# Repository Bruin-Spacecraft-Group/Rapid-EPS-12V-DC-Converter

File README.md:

# Rapid-EPS-12V-DC-Converter
PCB, operational instructions, other random stuff for use on 12V line for Rapid.

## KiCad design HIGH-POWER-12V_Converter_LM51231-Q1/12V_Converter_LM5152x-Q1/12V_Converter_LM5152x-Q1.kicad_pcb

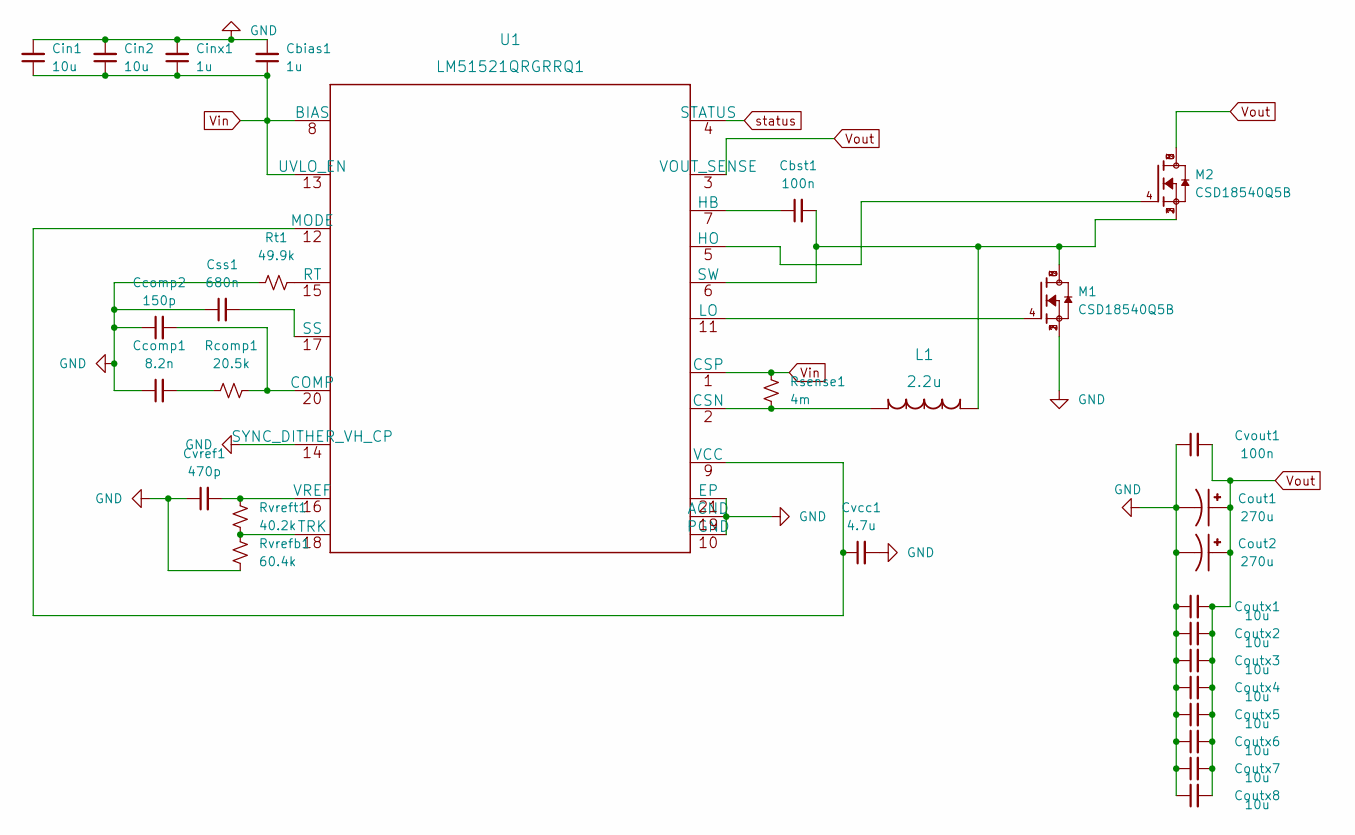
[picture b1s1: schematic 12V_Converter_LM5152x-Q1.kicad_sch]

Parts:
Cbias1: 1u; C_0603_1608Metric; LCSC C92759
Cbst1: 100n; C_0603_1608Metric; LCSC C92759
Ccomp1: 8.2n; C_0805_2012Metric
Ccomp2: 150p; C_0805_2012Metric; LCSC C107111
Cin1, Cin2: 10u; C_1206_3216Metric; LCSC C77093
Cinx1: 1u; C_0603_1608Metric; LCSC C2172920
Cout1, Cout2: 270u; CAP_EEHZS1H271UP
Coutx1, Coutx2, Coutx3, Coutx4, Coutx5, Coutx6, Coutx7, Coutx8: 10u; C_1206_3216Metric; LCSC C77093
Css1: 680n; C_0603_1608Metric
Cvcc1: 4.7u; C_0603_1608Metric
Cvout1: 100n; C_0603_1608Metric; LCSC C2842861
Cvref1: 470p; C_0603_1608Metric; LCSC C85979
L1: 2.2u; IHLP6767GZER2R2M51
M1, M2: CSD18540Q5B; TRANS_CSD18540Q5B; PARTREV B
Rcomp1: 20.5k; R_0603_1608Metric; LCSC C273789
Rsense1: 4m; R_2512_6332Metric
Rt1: 49.9k; R_0603_1608Metric; LCSC C844171
Rvrefb1: 60.4k; R_0603_1608Metric; LCSC C165742
Rvreft1: 40.2k; R_0603_1608Metric; LCSC C844784
U1: LM51521QRGRRQ1

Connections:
GND: Cbias1.2, Ccomp1.1, Ccomp2.1, Cin1.2, Cin2.2, Cinx1.2, Cout1.2, Cout2.2, Coutx1.1, Coutx2.1, Coutx3.1, Coutx4.1, Coutx5.1, Coutx6.1, Coutx7.1, Coutx8.1, Css1.1, Cvcc1.2, Cvout1.1, Cvref1.1, M1.1, M1.2, M1.3, Rt1.1, Rvrefb1.2, U1.10 (PGND), U1.14 (SYNC_DITHER_VH_CP), U1.19 (AGND), U1.21 (EP)
unnamed: Cbst1.1, U1.7 (HB)
unnamed: Cbst1.2, L1.1, M1.5, M1.6, M1.7, M1.8, M2.1, M2.2, M2.3, U1.6 (SW)
unnamed: Ccomp1.2, Rcomp1.1
unnamed: Ccomp2.2, Rcomp1.2, U1.20 (COMP)
unnamed: Css1.2, U1.17 (SS)
unnamed: Cvcc1.1, U1.9 (VCC), U1.12 (MODE)
unnamed: Cvref1.2, Rvreft1.1, U1.16 (VREF)
unnamed: L1.2, Rsense1.2, U1.2 (CSN)
unnamed: M2.4, U1.5 (HO)
unnamed: Rt1.2, U1.15 (RT)
unnamed: Rvrefb1.1, Rvreft1.2, U1.18 (TRK)
unnamed: M1.4, U1.11 (LO)
Vin: Cbias1.1, Cin1.1, Cin2.1, Cinx1.1, Rsense1.1, U1.1 (CSP), U1.8 (BIAS), U1.13 (UVLO_EN)
Vout: Cout1.1, Cout2.1, Coutx1.2, Coutx2.2, Coutx3.2, Coutx4.2, Coutx5.2, Coutx6.2, Coutx7.2, Coutx8.2, Cvout1.2, M2.5, M2.6, M2.7, M2.8, U1.3 (VOUT_SENSE)
status: U1.4 (STATUS); also elsewhere on the board

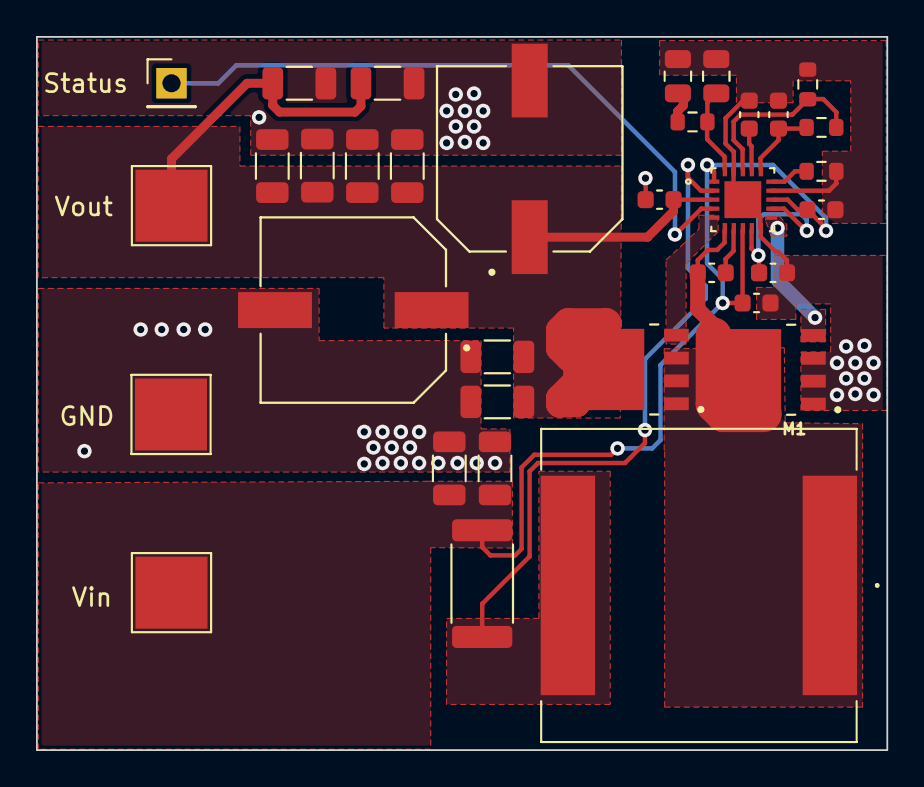
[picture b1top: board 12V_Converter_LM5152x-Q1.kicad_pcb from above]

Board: 2 copper layers, 47.2 x 39.6 mm, 31 parts (0 on the bottom side), 16 nets.

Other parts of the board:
Status: PinHeader_1x01_P2.54mm_Vertical

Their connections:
status: Status.1; also elsewhere on the board

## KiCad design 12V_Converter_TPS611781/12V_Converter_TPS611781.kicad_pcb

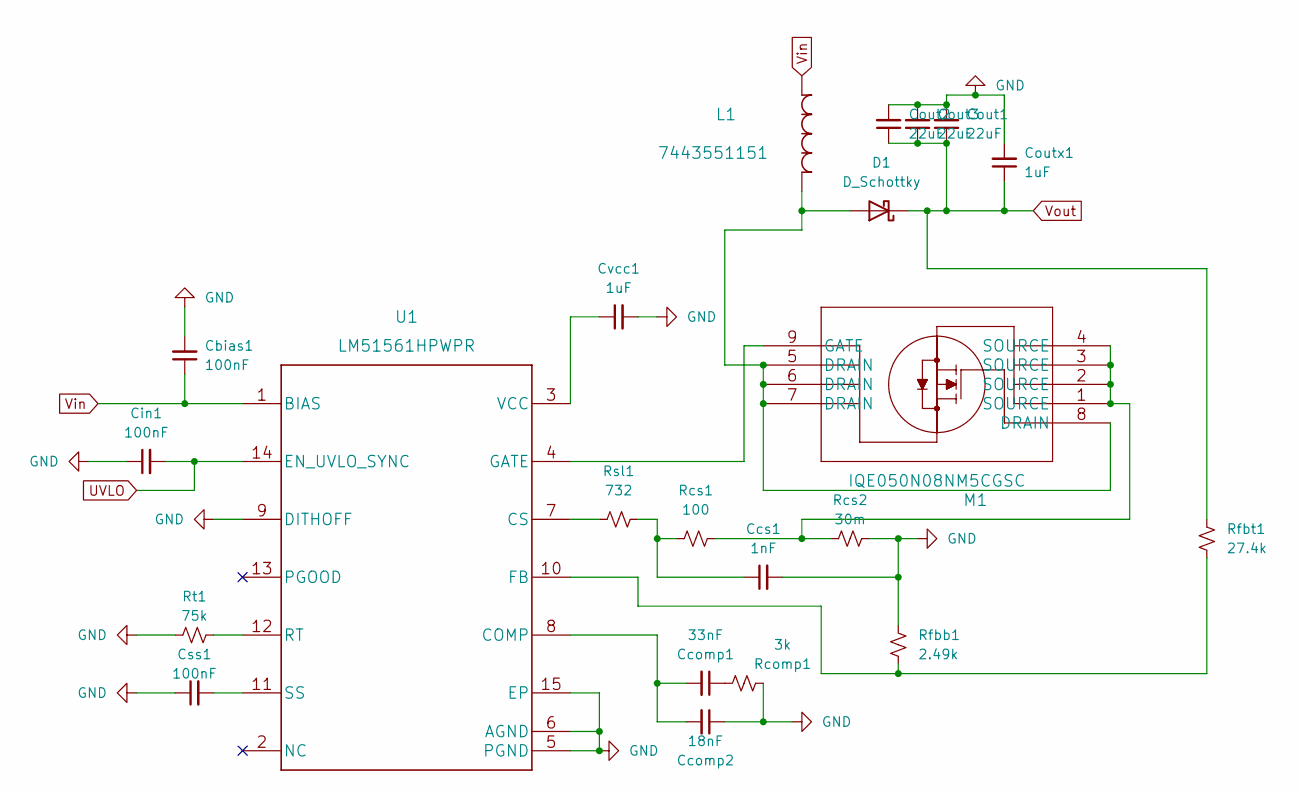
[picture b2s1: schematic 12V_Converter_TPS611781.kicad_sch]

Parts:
Cbias1: 100nF; C_0805_2012Metric
Ccomp1: 33nF; C_0805_2012Metric
Ccomp2: 18nF; C_0805_2012Metric
Ccs1: 1nF; C_0805_2012Metric
Cin1: 100nF; C_1206_3216Metric
Cout1, Cout2, Cout3: 22uF; C_1210_3225Metric
Coutx1: 1uF; C_0805_2012Metric
Css1: 100nF; C_0805_2012Metric
Cvcc1: 1uF; C_0603_1608Metric
D1: D_Schottky; D_SOD-128
L1: 7443551151
M1: IQE050N08NM5CGSC; IQE050N08NM5CGATMA1
Rcomp1: 3k; R_0603_1608Metric
Rcs1: 100; R_0805_2012Metric
Rcs2: 30m; R_1206_3216Metric
Rfbb1: 2.49k; R_0603_1608Metric
Rfbt1: 27.4k; R_0603_1608Metric
Rsl1: 732; R_0805_2012Metric
Rt1: 75k; R_0805_2012Metric
U1: LM51561HPWPR

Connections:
GND: Cbias1.2, Ccomp2.1, Ccs1.2, Cin1.1, Cout1.2, Cout2.2, Cout3.2, Coutx1.2, Css1.1, Cvcc1.2, Rcomp1.1, Rcs2.2, Rfbb1.2, Rt1.1, U1.5 (PGND), U1.6 (AGND), U1.9 (DITHOFF), U1.15 (EP); also elsewhere on the board
unnamed: Ccomp1.1, Rcomp1.2
unnamed: Ccomp1.2, Ccomp2.2, U1.8 (COMP)
unnamed: Ccs1.1, Rcs1.1, Rsl1.2
unnamed: Css1.2, U1.11 (SS)
unnamed: Cvcc1.1, U1.3 (VCC)
unnamed: D1.2 (A), L1.1, M1.5 (DRAIN), M1.6 (DRAIN), M1.7 (DRAIN), M1.8 (DRAIN)
unnamed: M1.9 (GATE), U1.4 (GATE)
unnamed: M1.1 (SOURCE), M1.2 (SOURCE), M1.3 (SOURCE), M1.4 (SOURCE), Rcs1.2, Rcs2.1
unnamed: Rfbb1.1, Rfbt1.1, U1.10 (FB)
unnamed: Rsl1.1, U1.7 (CS)
unnamed: Rt1.2, U1.12 (RT)
UVLO: Cin1.2, U1.14 (EN_UVLO_SYNC)
Vin: Cbias1.1, L1.2, U1.1 (BIAS)
Vout: Cout1.1, Cout2.1, Cout3.1, Coutx1.1, D1.1 (K), Rfbt1.2; also elsewhere on the board

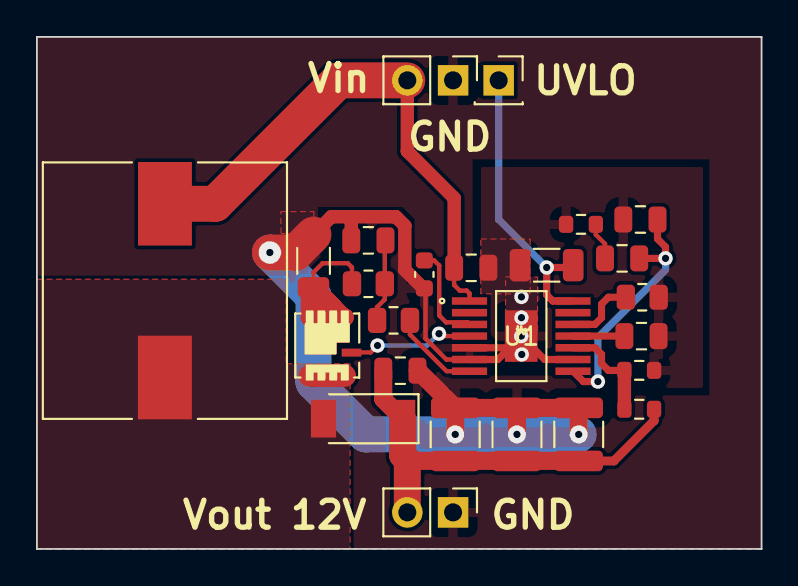
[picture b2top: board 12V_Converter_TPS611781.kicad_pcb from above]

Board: 2 copper layers, 40.3 x 28.4 mm, 23 parts (0 on the bottom side), 15 nets.

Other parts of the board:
REF: PinHeader_1x02_P2.54mm_Vertical

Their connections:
GND: REF.1; also elsewhere on the board
Vout: REF.2; also elsewhere on the board

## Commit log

2023-01-29 created initial pcb
2023-01-29 remove backups
2023-01-30 changed components
    - changed inductor to be better resistance
    - changed ic to be qfp instead of qfn
    - changed N MOSFET to be 100V instead of 30V
    - separated UVLO from Vin to allow for UVLO operation if needed (added external connect pin)
2023-01-30 notes on diodes
2023-01-30 actually added pcb edge
2023-01-30 got rid of soldermask on component
2023-01-30 remove auto_saved_files
2023-01-30 fesafw3eef
2023-01-30 made things better :)
    moved current sense resistor closer to the spot that senses the current
2023-01-30 reduced switching loop area
2023-01-30 corrected vin location on schematic
2023-01-30 shifted traces
2023-01-30 made traces chonky
2023-01-30 made traces EXTRA CHONKY
2023-01-30 made more traces chonky
2023-01-30 bro idek
2023-01-30 dwdgwyauwahuwaefe
2023-01-30 updated cvcc orientation
2023-01-30 closed closer loop
2023-01-30 shifted some things over to the right and got rid of the ground river in the middle
2023-01-30 shifted trace to actually align with vout lolololololo
2023-01-30 got rid of the massive short
2023-01-30 moved gnd silkmask
2023-01-30 fix GND side of current sense probe and DRC issues
2023-01-30 improve thermals
2023-01-30 added back the auxiliary diodes, which got annhialated for some reason
2023-01-31 created gerber files
2023-03-07 created high power 12V converter schematic and pcb
2023-03-07 added some jlcpcb pick n place files
2023-03-07 updated current sense line
2023-03-07 ngl idek
2023-03-07 adwrhnrsrtygfhb
2023-03-08 updated from reviews
    - changed capacitor
    - changed output capacitors
    - moved a bunch of stuff around and filled in a lot of copper area
2023-03-08 made some changed
2023-03-08 changed folder name
2023-03-08 added bom sheet and actually added a pcb border
2023-04-18 updated mosfets on high power 12V
2023-04-19 add review notes
2023-04-21 updated high power to reflect changes described in review notes
2023-04-25 literally not a clue what i did i think i made some gerber files or smth

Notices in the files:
parts and their libraries:
Copyright 2021 Accelerated Designs. All rights reserved.
